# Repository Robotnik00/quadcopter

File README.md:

quadcopter
==========

rc quadcopter

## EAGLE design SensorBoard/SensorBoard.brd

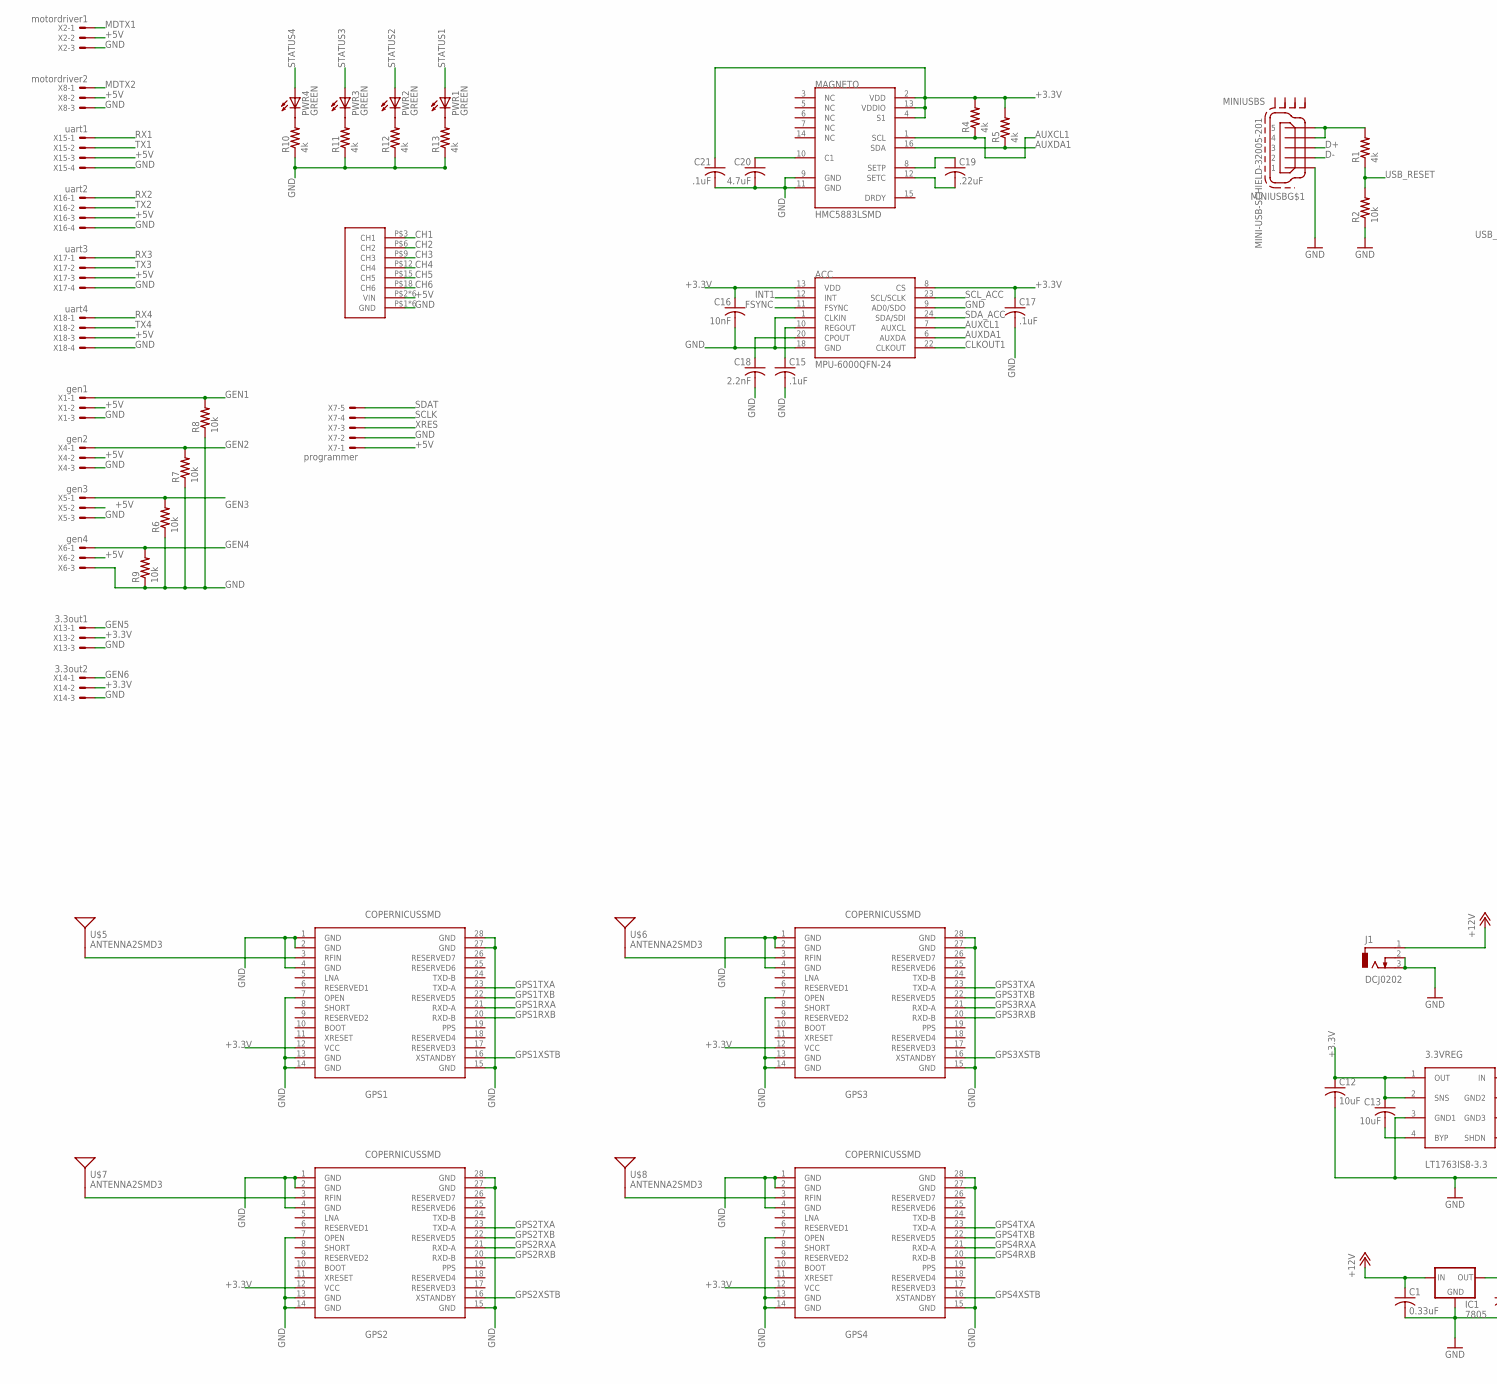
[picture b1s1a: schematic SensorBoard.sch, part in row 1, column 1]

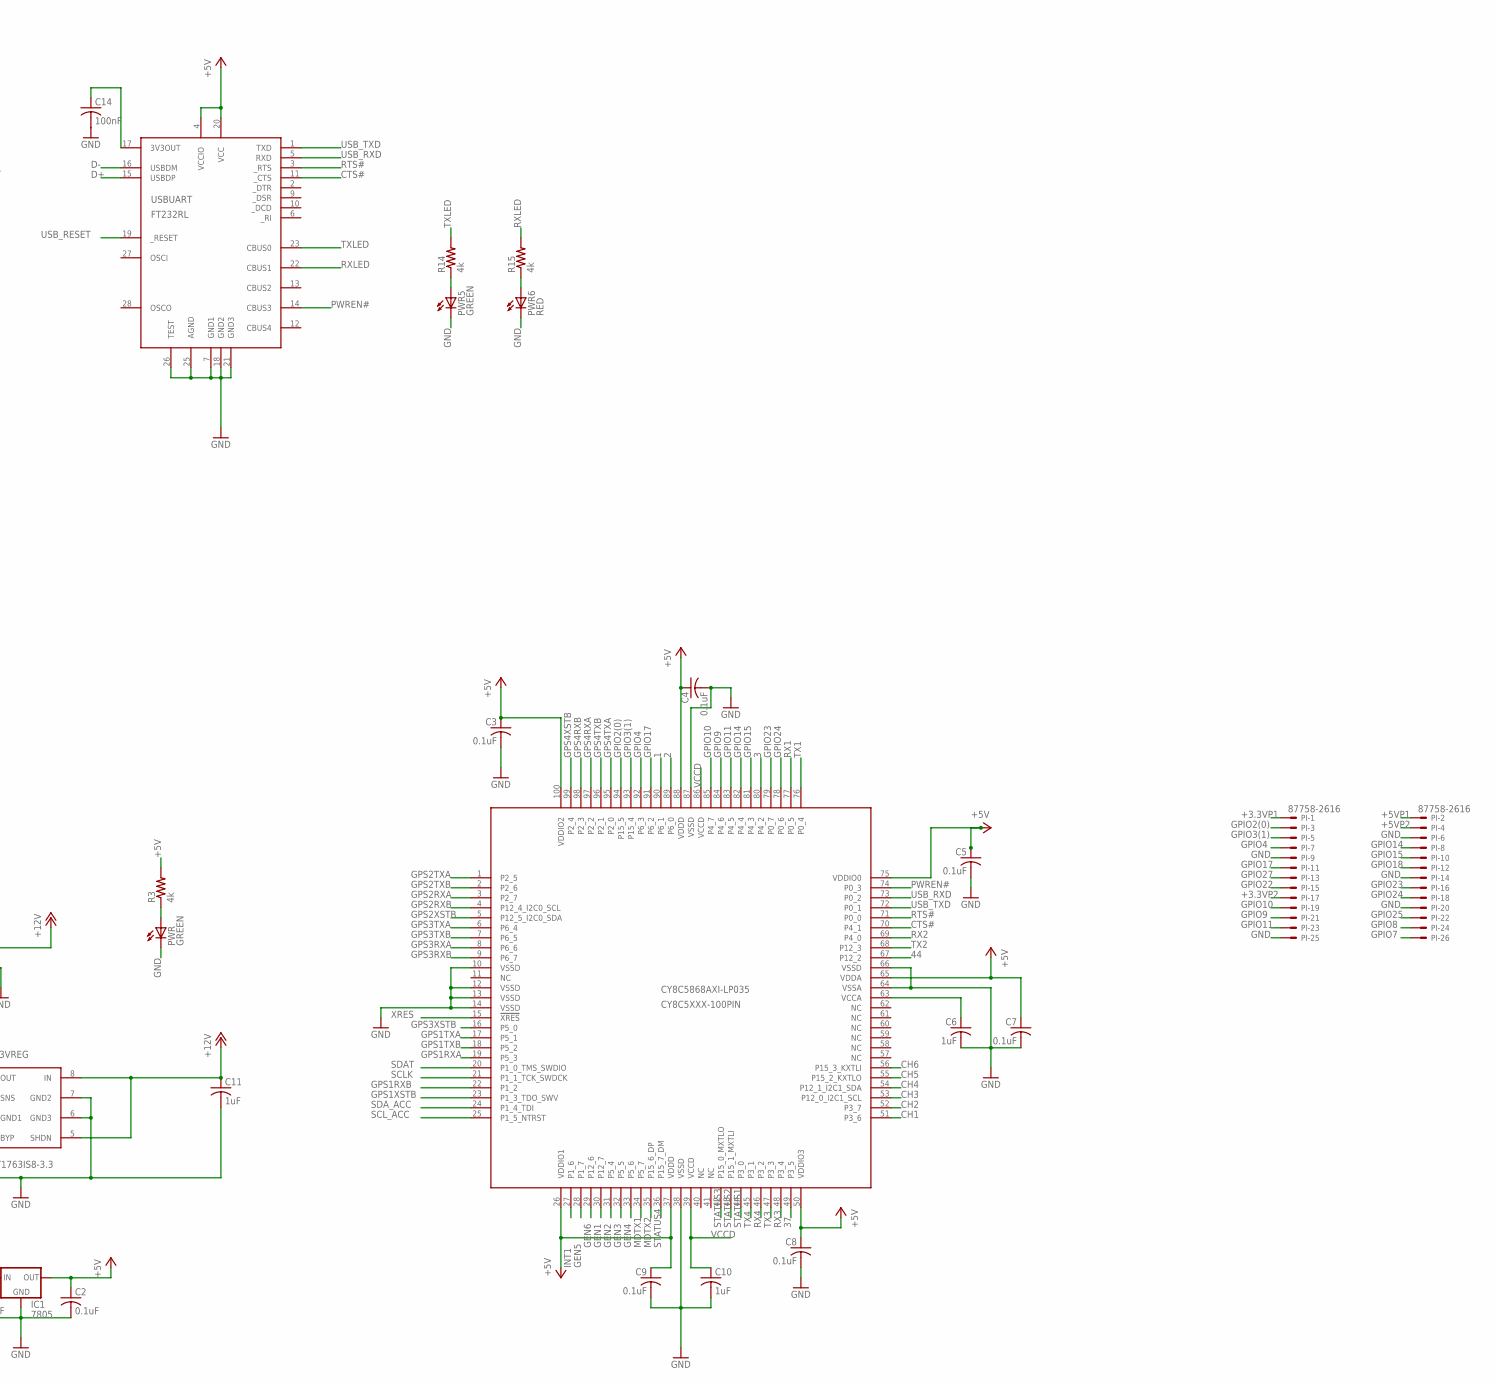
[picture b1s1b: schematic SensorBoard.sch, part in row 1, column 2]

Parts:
3.3VREG: LT1763IS8-3.3; LT1763IS8-SMD
ACC: MPU-6000QFN-24; QFN-24-TESTING
C1: 0.33uF; C0402
C2, C3, C4, C5, C7, C8, C9: 0.1uF; C0402
C6, C10, C11: 1uF; C0402
C12, C13: 10uF; C0402
C14: 100nF; C0402
C15, C17, C21: .1uF; C0402
C16: 10nF; C0402
C18: 2.2nF; C0402
C19: .22uF; C0402
C20: 4.7uF; C0402
CY8C5868AXI-LP035: CY8C5XXX-100PIN; TQFP-14X14-100
GPS1, GPS2, GPS3, GPS4: COPERNICUSSMD; COPERNICUS
IC1: 7805; 78XXL
J1: DCJ0202
MAGNETO: HMC5883LSMD; 16LPCC
MINIUSB: MINI-USB-SCHIELD-32005-201; 32005-201
PI: 87758-2616
PWR, PWR1, PWR2, PWR3, PWR4, PWR5: GREEN; CHIP-LED0603
PWR6: RED; CHIP-LED0603
R1, R3, R4, R5, R10, R11, R12, R13, R14, R15: 4k; 0204/5
R2, R6, R7, R8, R9: 10k; 0204/5
RC: 6-CHANNEL
U$5, U$6, U$7, U$8: ANTENNA2SMD3; ANTENNA-CHIP4
USBUART: FT232RL; SSOP28DB
X1: gen1; KK-156-3
X2: motordriver1; KK-156-3
X4: gen2; KK-156-3
X5: gen3; KK-156-3
X6: gen4; KK-156-3
X7: programmer; KK-156-5
X8: motordriver2; KK-156-3
X13: 3.3out1; KK-156-3
X14: 3.3out2; KK-156-3
X15: uart1; KK-156-4
X16: uart2; KK-156-4
X17: uart3; KK-156-4
X18: uart4; KK-156-4

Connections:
1: CY8C5868AXI-LP035.90 (P6_1)
2: CY8C5868AXI-LP035.89 (P6_0)
3: CY8C5868AXI-LP035.80 (P4_2)
37: CY8C5868AXI-LP035.49 (P3_5)
44: CY8C5868AXI-LP035.67 (P12_2)
+3.3V: 3.3VREG.1 (OUT), 3.3VREG.2 (SNS), ACC.8 (CS), ACC.13 (VDD), C12.1, C13.1, C16.1, C17.1, C21.1, GPS1.12 (VCC), GPS2.12 (VCC), GPS3.12 (VCC), GPS4.12 (VCC), MAGNETO.2 (VDD), MAGNETO.4 (S1), MAGNETO.13 (VDDIO), R4.2, R5.2, X13.2, X14.2
+3.3VP1: PI.1
+3.3VP2: PI.17
+5V: C2.1, C3.1, C4.1, C5.1, C7.1, C8.1, C9.1, CY8C5868AXI-LP035.26 (VDDIO1), CY8C5868AXI-LP035.37 (VDDD), CY8C5868AXI-LP035.50 (VDDIO3), CY8C5868AXI-LP035.65 (VDDA), CY8C5868AXI-LP035.75 (VDDIO0), CY8C5868AXI-LP035.88 (VDDD), CY8C5868AXI-LP035.100 (VDDIO2), IC1.OUT, R3.2, RC.P$2 (VIN), RC.P$5 (VIN), RC.P$8 (VIN), RC.P$11 (VIN), RC.P$14 (VIN), RC.P$17 (VIN), USBUART.4 (VCCIO), USBUART.20 (VCC), X1.2, X2.2, X4.2, X5.2, X6.2, X7.1, X8.2, X15.3, X16.3, X17.3, X18.3
+5VP1: PI.2
+5VP2: PI.4
+12V: 3.3VREG.5 (SHDN), 3.3VREG.8 (IN), C1.1, C11.1, IC1.IN, J1.1
AUXCL1: ACC.7 (AUXCL), MAGNETO.1 (SCL), R4.1
AUXDA1: ACC.6 (AUXDA), MAGNETO.16 (SDA), R5.1
CH1: CY8C5868AXI-LP035.51 (P3_6), RC.P$3 (CH1)
CH2: CY8C5868AXI-LP035.52 (P3_7), RC.P$6 (CH2)
CH3: CY8C5868AXI-LP035.53 (P12_0_I2C1_SCL), RC.P$9 (CH3)
CH4: CY8C5868AXI-LP035.54 (P12_1_I2C1_SDA), RC.P$12 (CH4)
CH5: CY8C5868AXI-LP035.55 (P15_2_KXTLO), RC.P$15 (CH5)
CH6: CY8C5868AXI-LP035.56 (P15_3_KXTLI), RC.P$18 (CH6)
CLKOUT1: ACC.22 (CLKOUT)
CTS#: CY8C5868AXI-LP035.70 (P4_1), USBUART.11 (_CTS)
D+: MINIUSB.3, USBUART.15 (USBDP)
D-: MINIUSB.2, USBUART.16 (USBDM)
FSYNC: ACC.11 (FSYNC)
GEN1: CY8C5868AXI-LP035.30 (P12_7), R8.2, X1.1
GEN2: CY8C5868AXI-LP035.31 (P5_4), R7.2, X4.1
GEN3: CY8C5868AXI-LP035.32 (P5_5), R6.2, X5.1
GEN4: CY8C5868AXI-LP035.33 (P5_6), R9.2, X6.1
GEN5: CY8C5868AXI-LP035.28 (P1_7), X13.1
GEN6: CY8C5868AXI-LP035.29 (P12_6), X14.1
GND: 3.3VREG.3 (GND1), 3.3VREG.6 (GND3), 3.3VREG.7 (GND2), ACC.1 (CLKIN), ACC.9 (AD0/SDO), ACC.18 (GND), C1.2, C2.2, C3.2, C4.2, C5.2, C6.2, C7.2, C8.2, C9.2, C10.2, C11.2, C12.2, C14.2, C15.2, C16.2, C17.2, C18.2, C20.2, C21.2, CY8C5868AXI-LP035.10 (VSSD), CY8C5868AXI-LP035.12 (VSSD), CY8C5868AXI-LP035.13 (VSSD), CY8C5868AXI-LP035.14 (VSSD), CY8C5868AXI-LP035.38 (VSSD), CY8C5868AXI-LP035.64 (VSSA), CY8C5868AXI-LP035.66 (VSSD), CY8C5868AXI-LP035.87 (VSSD), GPS1.1 (GND), GPS1.2 (GND), GPS1.4 (GND), GPS1.7 (OPEN), GPS1.13 (GND), GPS1.14 (GND), GPS1.15 (GND), GPS1.27 (GND), GPS1.28 (GND), GPS2.1 (GND), GPS2.2 (GND), GPS2.4 (GND), GPS2.7 (OPEN), GPS2.13 (GND), GPS2.14 (GND), GPS2.15 (GND), GPS2.27 (GND), GPS2.28 (GND), GPS3.1 (GND), GPS3.2 (GND), GPS3.4 (GND), GPS3.7 (OPEN), GPS3.13 (GND), GPS3.14 (GND), GPS3.15 (GND), GPS3.27 (GND), GPS3.28 (GND), GPS4.1 (GND), GPS4.2 (GND), GPS4.4 (GND), GPS4.7 (OPEN), GPS4.13 (GND), GPS4.14 (GND), GPS4.15 (GND), GPS4.27 (GND), GPS4.28 (GND), IC1.GND, J1.2, J1.3, MAGNETO.9 (GND), MAGNETO.11 (GND), MINIUSB.1, PI.6, PI.9, PI.14, PI.20, PI.25, PWR.C, PWR5.C, PWR6.C, R2.1, R6.1, R7.1, R8.1, R9.1, R10.1, R11.1, R12.1, R13.1, RC.P$1 (GND), RC.P$4 (GND), RC.P$7 (GND), RC.P$10 (GND), RC.P$13 (GND), RC.P$16 (GND), USBUART.7 (GND1), USBUART.18 (GND2), USBUART.21 (GND3), USBUART.25 (AGND), USBUART.26 (TEST), X1.3, X2.3, X4.3, X5.3, X6.3, X7.2, X8.3, X13.3, X14.3, X15.4, X16.4, X17.4, X18.4
GPIO2(0): CY8C5868AXI-LP035.94 (P15_5), PI.3
GPIO3(1): CY8C5868AXI-LP035.93 (P15_4), PI.5
GPIO4: CY8C5868AXI-LP035.92 (P6_3), PI.7
GPIO7: PI.26
GPIO8: PI.24
GPIO9: CY8C5868AXI-LP035.84 (P4_6), PI.21
GPIO10: CY8C5868AXI-LP035.85 (P4_7), PI.19
GPIO11: CY8C5868AXI-LP035.83 (P4_5), PI.23
GPIO14: CY8C5868AXI-LP035.82 (P4_4), PI.8
GPIO15: CY8C5868AXI-LP035.81 (P4_3), PI.10
GPIO17: CY8C5868AXI-LP035.91 (P6_2), PI.11
GPIO18: PI.12
GPIO22: PI.15
GPIO23: CY8C5868AXI-LP035.79 (P0_7), PI.16
GPIO24: CY8C5868AXI-LP035.78 (P0_6), PI.18
GPIO25: PI.22
GPIO27: PI.13
GPS1RXA: CY8C5868AXI-LP035.19 (P5_3), GPS1.21 (RXD-A)
GPS1RXB: CY8C5868AXI-LP035.22 (P1_2), GPS1.20 (RXD-B)
GPS1TXA: CY8C5868AXI-LP035.17 (P5_1), GPS1.23 (TXD-A)
GPS1TXB: CY8C5868AXI-LP035.18 (P5_2), GPS1.22 (RESERVED5)
GPS1XSTB: CY8C5868AXI-LP035.23 (P1_3_TDO_SWV), GPS1.16 (XSTANDBY)
GPS2RXA: CY8C5868AXI-LP035.3 (P2_7), GPS2.21 (RXD-A)
GPS2RXB: CY8C5868AXI-LP035.4 (P12_4_I2C0_SCL), GPS2.20 (RXD-B)
GPS2TXA: CY8C5868AXI-LP035.1 (P2_5), GPS2.23 (TXD-A)
GPS2TXB: CY8C5868AXI-LP035.2 (P2_6), GPS2.22 (RESERVED5)
GPS2XSTB: CY8C5868AXI-LP035.5 (P12_5_I2C0_SDA), GPS2.16 (XSTANDBY)
GPS3RXA: CY8C5868AXI-LP035.8 (P6_6), GPS3.21 (RXD-A)
GPS3RXB: CY8C5868AXI-LP035.9 (P6_7), GPS3.20 (RXD-B)
GPS3TXA: CY8C5868AXI-LP035.6 (P6_4), GPS3.23 (TXD-A)
GPS3TXB: CY8C5868AXI-LP035.7 (P6_5), GPS3.22 (RESERVED5)
GPS3XSTB: CY8C5868AXI-LP035.16 (P5_0), GPS3.16 (XSTANDBY)
GPS4RXA: CY8C5868AXI-LP035.97 (P2_2), GPS4.21 (RXD-A)
GPS4RXB: CY8C5868AXI-LP035.98 (P2_3), GPS4.20 (RXD-B)
GPS4TXA: CY8C5868AXI-LP035.95 (P2_0), GPS4.23 (TXD-A)
GPS4TXB: CY8C5868AXI-LP035.96 (P2_1), GPS4.22 (RESERVED5)
GPS4XSTB: CY8C5868AXI-LP035.99 (P2_4), GPS4.16 (XSTANDBY)
INT1: ACC.12 (INT), CY8C5868AXI-LP035.27 (P1_6)
MDTX1: CY8C5868AXI-LP035.34 (P5_7), X2.1
MDTX2: CY8C5868AXI-LP035.35 (P15_6_DP), X8.1
unnamed: C6.1, CY8C5868AXI-LP035.63 (VCCA)
unnamed: 3.3VREG.4 (BYP), C13.2
unnamed: GPS1.3 (RFIN), U$5.SIG
unnamed: PWR.A, R3.1
unnamed: C14.1, USBUART.17 (3V3OUT)
unnamed: MINIUSB.4, MINIUSB.5, R1.2
unnamed: ACC.10 (REGOUT), C15.1
unnamed: ACC.20 (CPOUT), C18.1
unnamed: PWR4.C, R10.2
unnamed: GPS2.3 (RFIN), U$7.SIG
unnamed: C19.2, MAGNETO.12 (SETC)
unnamed: GPS3.3 (RFIN), U$6.SIG
unnamed: GPS4.3 (RFIN), U$8.SIG
unnamed: C19.1, MAGNETO.8 (SETP)
unnamed: C20.1, MAGNETO.10 (C1)
unnamed: PWR3.C, R11.2
unnamed: PWR2.C, R12.2
unnamed: PWR1.C, R13.2
unnamed: PWR5.A, R14.1
unnamed: PWR6.A, R15.1
PWREN#: CY8C5868AXI-LP035.74 (P0_3), USBUART.14 (CBUS3)
RTS#: CY8C5868AXI-LP035.71 (P0_0), USBUART.3 (_RTS)
RX1: CY8C5868AXI-LP035.77 (P0_5), X15.1
RX2: CY8C5868AXI-LP035.69 (P4_0), X16.1
RX3: CY8C5868AXI-LP035.48 (P3_4), X17.1
RX4: CY8C5868AXI-LP035.46 (P3_2), X18.1
RXLED: R15.2, USBUART.22 (CBUS1)
SCLK: CY8C5868AXI-LP035.21 (P1_1_TCK_SWDCK), X7.4
SCL_ACC: ACC.23 (SCL/SCLK), CY8C5868AXI-LP035.25 (P1_5_NTRST)
SDAT: CY8C5868AXI-LP035.20 (P1_0_TMS_SWDIO), X7.5
SDA_ACC: ACC.24 (SDA/SDI), CY8C5868AXI-LP035.24 (P1_4_TDI)
STATUS1: CY8C5868AXI-LP035.44 (P3_0), PWR1.A
STATUS2: CY8C5868AXI-LP035.43 (P15_1_MXTLI), PWR2.A
STATUS3: CY8C5868AXI-LP035.42 (P15_0_MXTLO), PWR3.A
STATUS4: CY8C5868AXI-LP035.36 (P15_7_DM), PWR4.A
TX1: CY8C5868AXI-LP035.76 (P0_4), X15.2
TX2: CY8C5868AXI-LP035.68 (P12_3), X16.2
TX3: CY8C5868AXI-LP035.47 (P3_3), X17.2
TX4: CY8C5868AXI-LP035.45 (P3_1), X18.2
TXLED: R14.2, USBUART.23 (CBUS0)
USB_RESET: R1.1, R2.2, USBUART.19 (_RESET)
USB_RXD: CY8C5868AXI-LP035.73 (P0_2), USBUART.5 (RXD)
USB_TXD: CY8C5868AXI-LP035.72 (P0_1), USBUART.1 (TXD)
VCCD: C10.1, CY8C5868AXI-LP035.39 (VCCD), CY8C5868AXI-LP035.86 (VCCD)
XRES: CY8C5868AXI-LP035.15 (!XRES!), X7.3

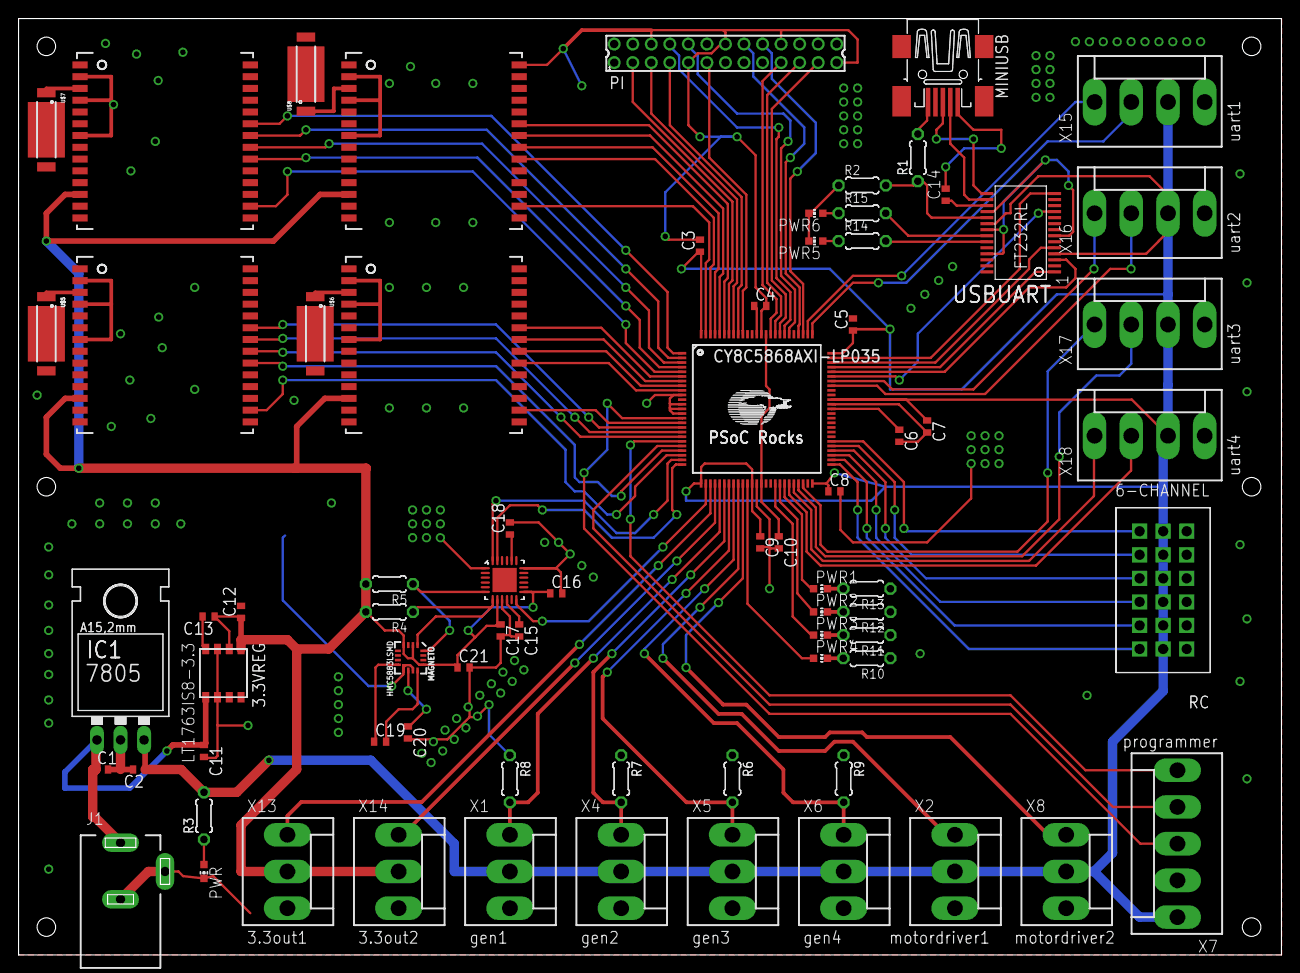
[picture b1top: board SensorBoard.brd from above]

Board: 2 copper layers, 136.2 x 101.0 mm, 74 parts (0 on the bottom side), 100 nets.

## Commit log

2013-06-06 added SensorBoard
2013-06-12 added interesting doc on combining GPS modules
2013-06-12 picked out my gps module
2013-06-13 Organized stuff
2013-06-13 moved some stuff around
2013-06-13 added board
2013-06-13 added stuff to board
2013-06-14 wired up wifi - jack
2013-06-16 Added Budget Spreadsheet to Project Docs folder
2013-06-16 wired up gps
2013-06-17 Added 3-axis compass to budget spreadsheet
2013-06-18 fixed pin
2013-06-18 added magnetometer
2013-06-18 added general pin io
2013-06-18 added psoc5 datasheet
2013-06-20 added Quadcoptor Project Outline
2013-06-23 finished schematic. All that is left is routing...
2013-06-26 fished SensorBoard. It is perrrfect! - jack
2013-06-26 added screw holes
2013-06-26 made drill holes larger for the rc
2013-06-27 most recent version of the board
2013-06-28 edited some stuff to make it pretty :]
2013-06-29 added chick :]
2013-06-29 board completely complete
2013-06-30 fixed some errors
2013-07-04 added gerbers
2013-07-05 okay now im done.
2013-07-07 added some more vias
2013-07-17 Added Unity Project containing Quadcoptor Sim
    Added to folder using a sym-link (windows mklink). Not sure if this
    commit will work as expected...

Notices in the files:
parts and their libraries:
SparkFun-RF: Licensing: CC v3.0 Share-Alike You are welcome to use this library for commercial purposes.
